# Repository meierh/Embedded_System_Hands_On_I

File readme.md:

# ESHO1 Group 07

## Group Project

All files related to the group project can be found in the `Project` folder. It contains the following parts of our project:

- [PCB Design](./Project/PCB)
- [Case Design](./Project/Case)
- Software
  - [High-Level Software with emulated hardware](./Project/Software/FLTK) (developed while the PCB was not finished yet)
  - [Full Software for our custom PCB](/Project/Software/CubeMX) (extension of the high-level software to work with the custom PCB)
- [Audio Files :smile:](./Project/DFPlayerAudio/production%20files)

The project documentation can be found [here](./Project/Documentation).

## Tasks 1 - 6

The full documentation of tasks 1 - 6 can be found [here](./Documentation_Tasks_1-6.pdf). Source code and additional files for each task can be found in the respective subfolders.

## Usage

- Ensure to clone submodules too

```bash
git submodule update --init --recursive
```

## Note

`.gitignore` contains an entry to ignore the folder "LOCAL" and all of its subfolders anywhere within this project.

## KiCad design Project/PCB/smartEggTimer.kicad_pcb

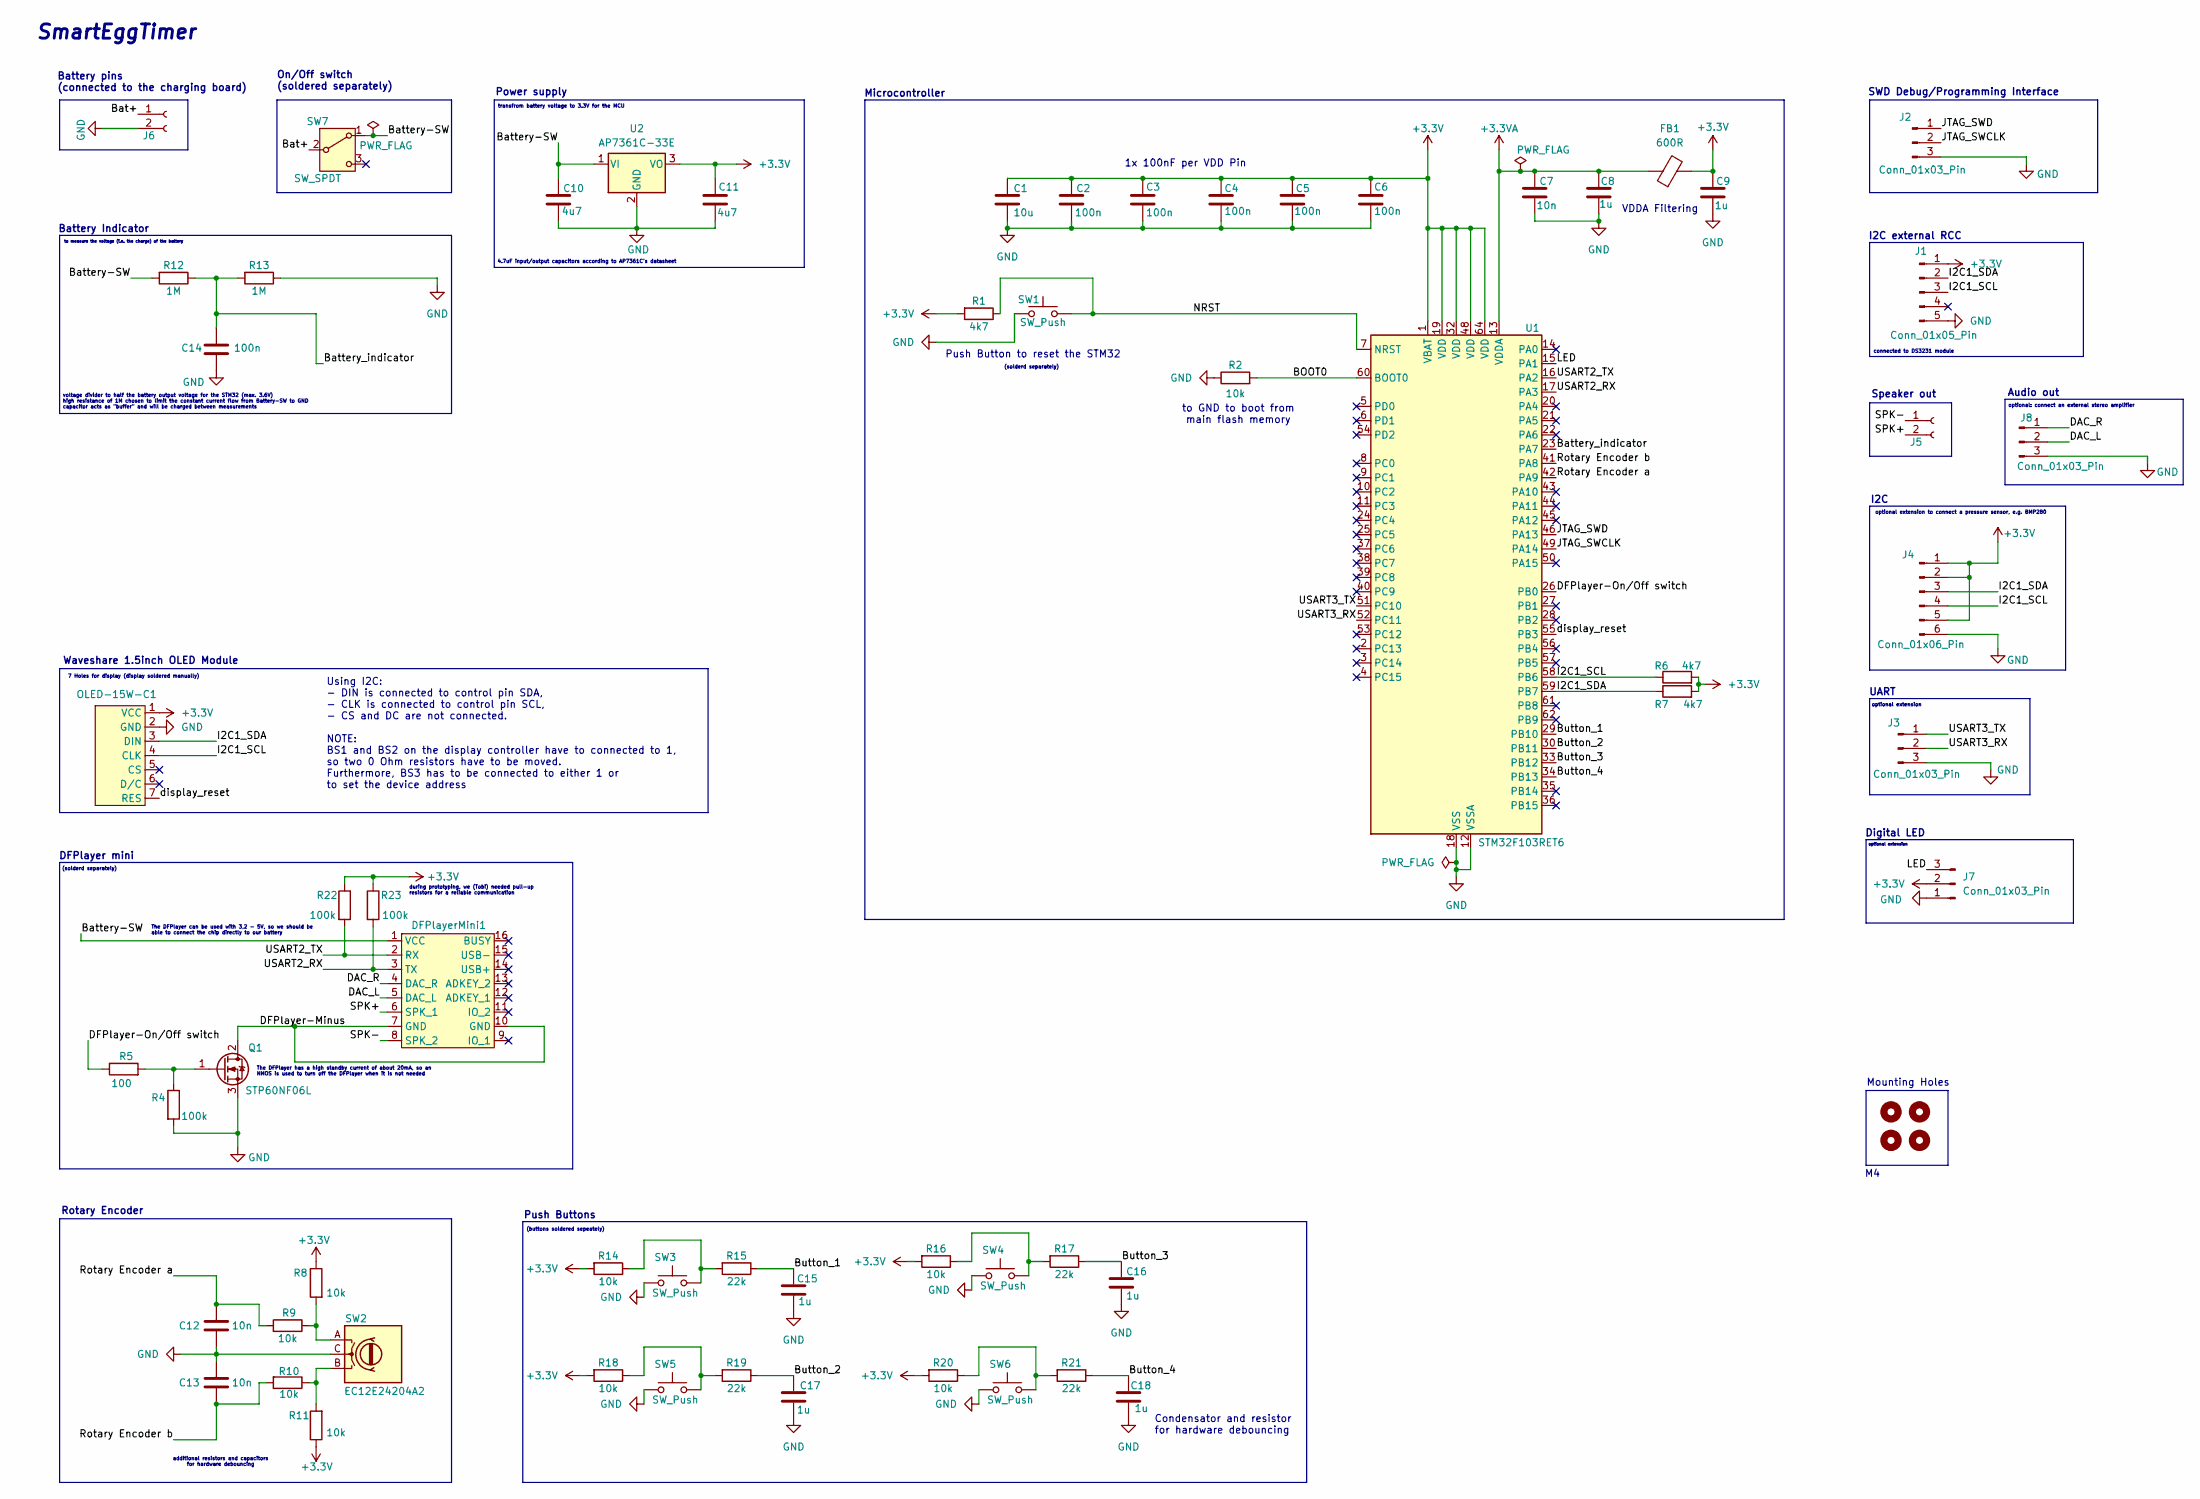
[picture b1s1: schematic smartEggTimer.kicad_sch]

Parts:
C1: 10u; C_0603_1608Metric; LCSC Part Number C19702
C2, C3, C4, C5, C6, C14: 100n; C_0402_1005Metric; LCSC Part Number C307331
C7, C12, C13: 10n; C_0402_1005Metric; LCSC Part Number C15195
C8, C9, C15, C16, C17, C18: 1u; C_0402_1005Metric; LCSC Part Number C52923
C10, C11: 4u7; C_0805_2012Metric; LCSC Part Number C1779
DFPlayerMini1: DFplayer-Mini
FB1: 600R; L_0603_1608Metric; LCSC Part Number C1002
H1, H2, H3, H8: MountingHole; MountingHole_4.3mm_M4_Without-Screws
J1: Conn_01x05_Pin; PinHeader_1x05_P2.54mm_Vertical
J2, J3, J7, J8: Conn_01x03_Pin; PinHeader_1x03_P2.54mm_Vertical
J4: Conn_01x06_Pin; PinHeader_1x06_P2.54mm_Vertical
J5, J6: Conn_01x02_Socket; PinHeader_1x02_P2.54mm_Vertical
OLED-15W-C1: PinSocket_1x07_P2.54mm_Vertical
Q1: STP60NF06L; TO-220-3_Vertical
R1, R6, R7: 4k7; R_0402_1005Metric; LCSC Part Number C25900
R2, R8, R9, R10, R11, R14, R16, R18, R20: 10k; R_0402_1005Metric; LCSC Part Number C25744
R4, R22, R23: 100k; R_0402_1005Metric; LCSC Part Number C25741
R5: 100; R_0402_1005Metric; LCSC Part Number C25076
R12, R13: 1M; R_0402_1005Metric; LCSC Part Number C26083
R15, R17, R19, R21: 22k; R_0402_1005Metric; LCSC Part Number C25768
SW1: SW_Push; SW_PUSH_6mm
SW2: EC12E24204A2; SW-TH_EC12E24204A2; LCSC Part Number C351238
SW3, SW4: SW_Push; SW_PUSH_6mm_H13mm
SW5: SW_Push; SW_PUSH_6mm_H13mm_No-Pad_Top-Right
SW6: SW_Push; SW_PUSH_6mm_H13mm_No-Pad_Top-Left
SW7: SW_SPDT; SW_Slide_SPDT_Angled_CK_OS102011MA1Q_Protruding
U1: STM32F103RET6; LQFP-64_L10.0-W10.0-P0.50-LS12.0-BL; LCSC Part Number C8322
U2: AP7361C-33E; SOT-223_L6.5-W3.5-P2.30-LS7.0-BR; LCSC Part Number C500795

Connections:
+3.3V: C1.1, C2.1, C3.1, C4.1, C5.1, C6.1, C9.1, C11.1, FB1.2, J1.1, J4.1, J4.2, J4.5, J7.2, OLED-15W-C1.1 (VCC), R1.2, R6.2, R7.2, R8.1, R11.1, R14.2, R16.2, R18.2, R20.2, R22.1, R23.1, U1.1 (VBAT), U1.19 (VDD), U1.32 (VDD), U1.48 (VDD), U1.64 (VDD), U2.3 (VO)
+3.3VA: C7.1, C8.1, FB1.1, U1.13 (VDDA)
/BOOT0: R2.2, U1.60 (BOOT0)
/Bat+: J6.1, SW7.2 (B)
/Battery-SW: C10.1, DFPlayerMini1.1 (VCC), R12.2, SW7.1 (A), U2.1 (VI)
/Battery_indicator: C14.1, R12.1, R13.2, U1.23 (PA7)
/Button_1: C15.1, R15.1, U1.29 (PB10)
/Button_2: C17.1, R19.1, U1.30 (PB11)
/Button_3: C16.1, R17.1, U1.33 (PB12)
/Button_4: C18.1, R21.1, U1.34 (PB13)
/DAC_L: DFPlayerMini1.5 (DAC_L), J8.2
/DAC_R: DFPlayerMini1.4 (DAC_R), J8.1
/DFPlayer-Minus: DFPlayerMini1.7 (GND), DFPlayerMini1.10 (GND), Q1.2 (D)
/DFPlayer-On/Off switch: R5.1, U1.26 (PB0)
/I2C1_SCL: J1.3, J4.4, OLED-15W-C1.4 (CLK), R6.1, U1.58 (PB6)
/I2C1_SDA: J1.2, J4.3, OLED-15W-C1.3 (DIN), R7.1, U1.59 (PB7)
/JTAG_SWCLK: J2.2, U1.49 (PA14)
/JTAG_SWD: J2.1, U1.46 (PA13)
/LED: J7.3, U1.15 (PA1)
/NRST: R1.1, SW1.2, U1.7 (NRST)
/Rotary Encoder a: C12.1, R9.2, U1.42 (PA9)
/Rotary Encoder b: C13.2, R10.2, U1.41 (PA8)
/SPK+: DFPlayerMini1.6 (SPK_1), J5.2
/SPK-: DFPlayerMini1.8 (SPK_2), J5.1
/USART2_RX: DFPlayerMini1.3 (TX), R23.2, U1.17 (PA3)
/USART2_TX: DFPlayerMini1.2 (RX), R22.2, U1.16 (PA2)
/USART3_RX: J3.2, U1.52 (PC11)
/USART3_TX: J3.1, U1.51 (PC10)
/display_reset: OLED-15W-C1.7 (RES), U1.55 (PB3)
GND: C1.2, C2.2, C3.2, C4.2, C5.2, C6.2, C7.2, C8.2, C9.2, C10.2, C11.2, C12.2, C13.1, C14.2, C15.2, C16.2, C17.2, C18.2, J1.5, J2.3, J3.3, J4.6, J6.2, J7.1, J8.3, OLED-15W-C1.2 (GND), Q1.3 (S), R2.1, R4.2, R13.1, SW1.1, SW2.C, SW3.1, SW4.1, SW5.1, SW6.1, U1.12 (VSSA), U1.18 (VSS), U1.31 (VSS), U1.47 (VSS), U1.63 (VSS), U2.2 (GND)
unnamed: Q1.1 (G), R4.1, R5.2
unnamed: R8.2, R9.1, SW2.A
unnamed: R10.1, R11.2, SW2.B
unnamed: R14.1, R15.2, SW3.2
unnamed: R16.1, R17.2, SW4.2
unnamed: R18.1, R19.2, SW5.2
unnamed: R20.1, R21.2, SW6.2

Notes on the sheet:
to measure the voltage (i.e. the charge) of the battery
1x 100nF per VDD Pin
Rotary Encoder
Speaker out
Waveshare 1.5inch OLED Module
Mounting Holes
optional extension
UART
transfrom battery voltage to 3.3V for the MCU
during prototyping, we (Tobi) needed pull-up resistors for a reliable communication
(solderd separately)
Microcontroller
voltage divider to half the battery output voltage for the STM32 (max. 3.6V) high resistance of 1M chosen to limit the constant current flow from Battery-SW to GND capacitor acts as "buffer" and will be charged between measurements
optional: connect an external stereo amplifier
4.7uF input/output capacitors according to AP7361C's datasheet
I2C
Power supply
(buttons soldered sepeately)
Condensator and resistor for hardware debouncing
Battery pins (connected to the charging board)
to GND to boot from main flash memory
connected to DS3231 module
Push Buttons
I2C external RCC
SmartEggTimer
DFPlayer mini
additional resistors and capacitors for hardware debouncing
SWD Debug/Programming Interface
The DFPlayer can be used with 3,2 - 5V, so we should be able to connect the chip directly to our battery
On/Off switch (soldered separately)
Push Button to reset the STM32
Audio out
VDDA Filtering
The DFPlayer has a high standby current of about 20mA, so an NMOS is used to turn off the DFPlayer when it is not needed
Battery Indicator
Using I2C: - DIN is connected to control pin SDA, - CLK is connected to control pin SCL, - CS and DC are not connected. NOTE: BS1 and BS2 on the display controller have to connected to 1, so two 0 Ohm resistors have to be moved. Furthermore, BS3 has to be connected to either 1 or to set the device 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
7 Holes for display (display soldered manually)
Digital LED
optional extension to connect a pressure sensor, e.g. BMP280

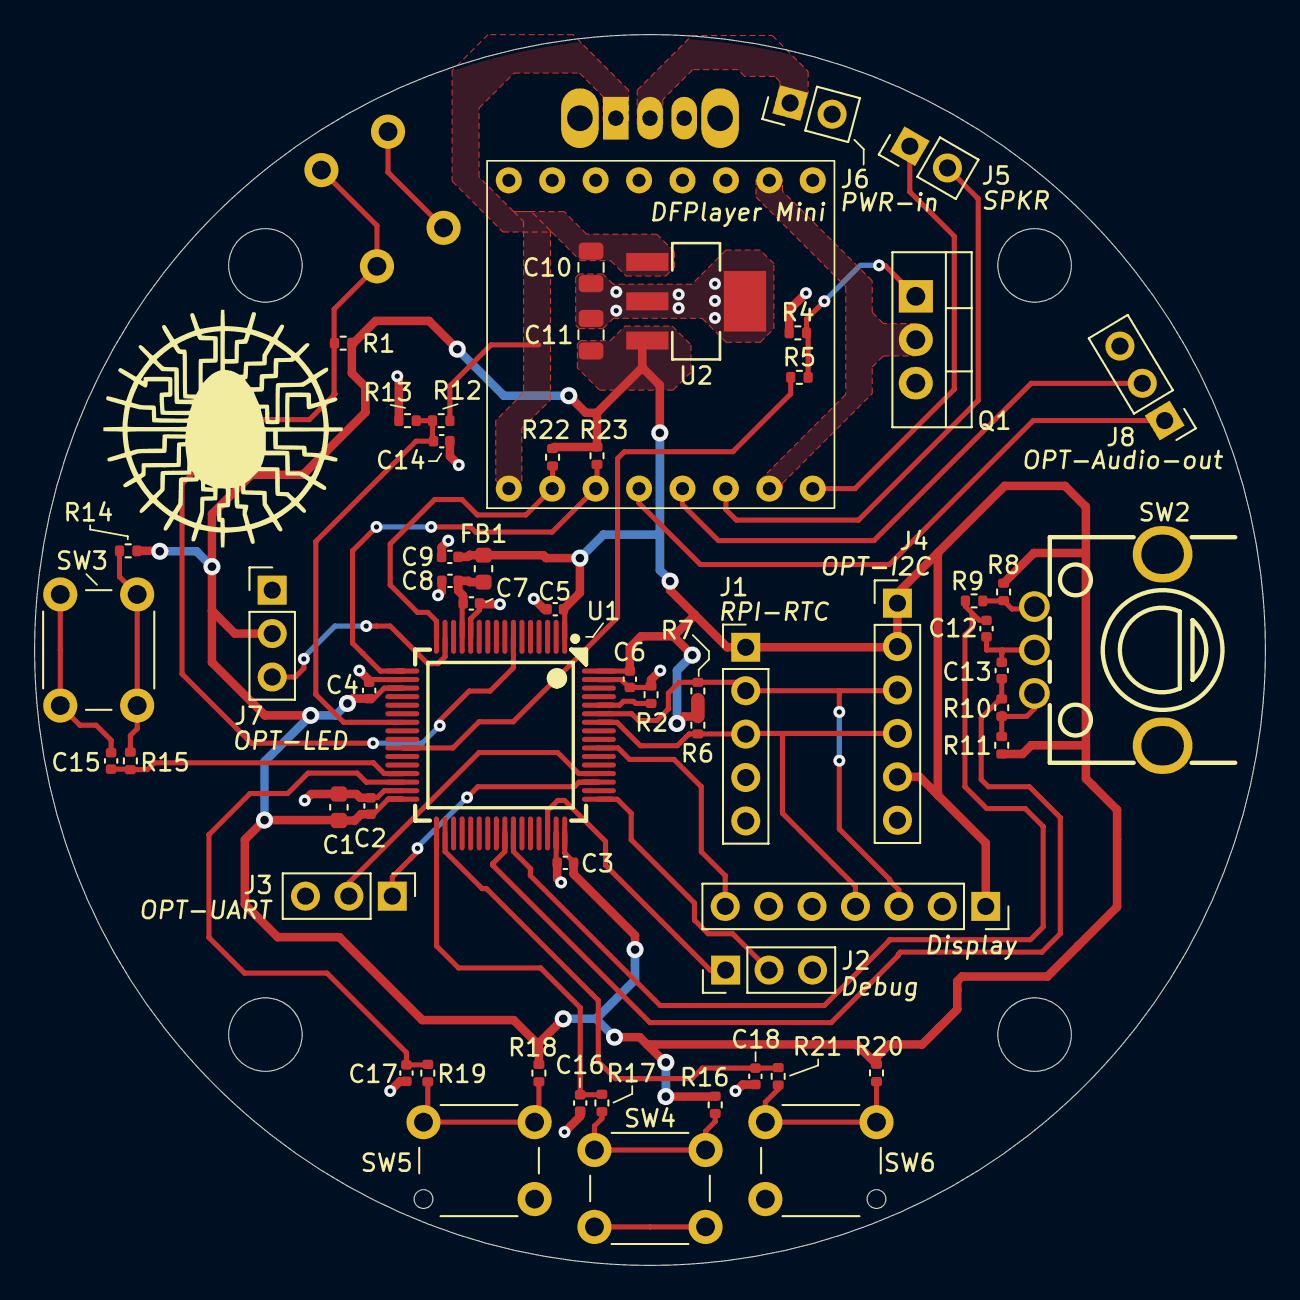
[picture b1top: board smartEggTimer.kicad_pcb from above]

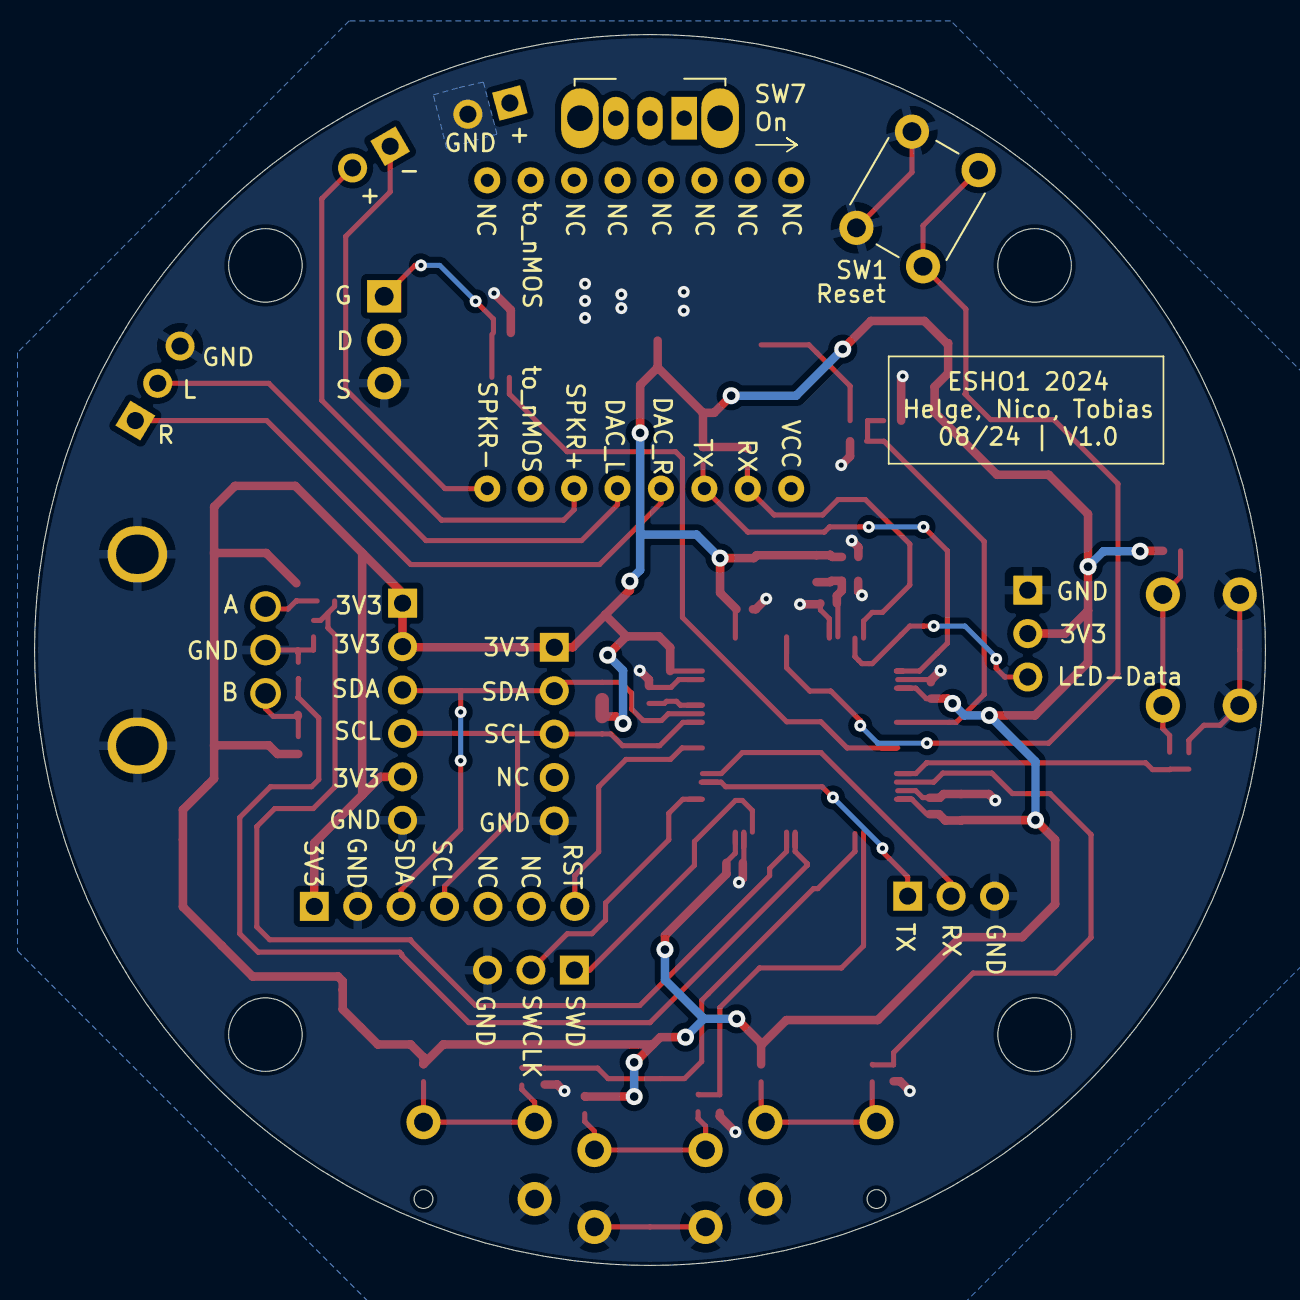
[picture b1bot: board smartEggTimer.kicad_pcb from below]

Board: 2 copper layers, 72.0 x 72.0 mm, 65 parts (2 on the bottom side), 37 nets.

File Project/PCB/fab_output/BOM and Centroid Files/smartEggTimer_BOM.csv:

"Value","Reference","Footprint","LCSC Part Number"
"10u","C1","C_0603_1608Metric","C19702"
"4u7","C10,C11","C_0805_2012Metric","C1779"
"100n","C2,C3,C4,C5,C6,C14","C_0402_1005Metric","C307331"
"10n","C7,C12,C13","C_0402_1005Metric","C15195"
"1u","C8,C9,C15,C16,C17,C18","C_0402_1005Metric","C52923"
"600R","FB1","L_0603_1608Metric","C1002"
"100","R5","R_0402_1005Metric","C25076"
"4k7","R1,R6,R7","R_0402_1005Metric","C25900"
"1M","R12,R13","R_0402_1005Metric","C26083"
"22k","R15,R17,R19,R21","R_0402_1005Metric","C25768"
"10k","R2,R8,R9,R10,R11,R14,R16,R18,R20","R_0402_1005Metric","C25744"
"100k","R4,R22,R23","R_0402_1005Metric","C25741"
"EC12E24204A2","SW2","SW-TH_EC12E24204A2","C351238"
"STM32F103RET6","U1","LQFP-64_L10.0-W10.0-P0.50-LS12.0-BL","C8322"
"AP7361C-33E","U2","SOT-223_L6.5-W3.5-P2.30-LS7.0-BR","C500795"

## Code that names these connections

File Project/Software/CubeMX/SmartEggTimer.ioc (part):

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Mcu.Name=STM32F103R(C-D-E)Tx
Mcu.Package=LQFP64
Mcu.UserName=STM32F103RETx
PA1.GPIOParameters=GPIO_Label
PA1.GPIO_Label=OPT_LED
PA1.Signal=S_TIM2_CH2
PA13.Mode=Serial_Wire
PA13.Signal=SYS_JTMS-SWDIO
PA14.Mode=Serial_Wire
PA14.Signal=SYS_JTCK-SWCLK
PA2.GPIOParameters=GPIO_Label
PA2.GPIO_Label=DFPlayer_USART_TX
PA2.Mode=Asynchronous
PA2.Signal=USART2_TX
PA3.GPIOParameters=GPIO_Label
PA3.GPIO_Label=DFPlayer_USART_RX
PA3.Mode=Asynchronous
PA3.Signal=USART2_RX
PA7.GPIOParameters=GPIO_Label
PA7.GPIO_Label=Battery_Indicator
PA7.Signal=ADCx_IN7
PA8.GPIOParameters=GPIO_Label,GPIO_ModeDefaultEXTI
PA8.GPIO_Label=Rotary_Encoder_B
PA8.GPIO_ModeDefaultEXTI=GPIO_MODE_IT_RISING_FALLING
PA8.Signal=GPXTI8
PA9.GPIOParameters=GPIO_Label,GPIO_ModeDefaultEXTI
PA9.GPIO_Label=Rotary_Encoder_A
PA9.GPIO_ModeDefaultEXTI=GPIO_MODE_IT_RISING_FALLING
PA9.Signal=GPXTI9
PB0.GPIOParameters=GPIO_Label
PB0.GPIO_Label=DFPlayer_On_Off
PB0.Signal=GPIO_Output
PB10.GPIOParameters=GPIO_Label,GPIO_ModeDefaultEXTI
PB10.GPIO_Label=Button_1
PB10.GPIO_ModeDefaultEXTI=GPIO_MODE_IT_FALLING
PB10.Signal=GPXTI10
PB11.GPIOParameters=GPIO_Label,GPIO_ModeDefaultEXTI
PB11.GPIO_Label=Button_2
PB11.GPIO_ModeDefaultEXTI=GPIO_MODE_IT_FALLING
PB11.Signal=GPXTI11
PB12.GPIOParameters=GPIO_Label,GPIO_ModeDefaultEXTI
PB12.GPIO_Label=Button_3
PB12.GPIO_ModeDefaultEXTI=GPIO_MODE_IT_FALLING
PB12.Signal=GPXTI12
PB13.GPIOParameters=GPIO_Label,GPIO_ModeDefaultEXTI
PB13.GPIO_Label=Button_4
PB13.GPIO_ModeDefaultEXTI=GPIO_MODE_IT_FALLING
PB13.Signal=GPXTI13
PB3.GPIOParameters=GPIO_Label
PB3.GPIO_Label=Display_Reset
PB3.Signal=GPIO_Output
PB6.Mode=I2C
PB6.Signal=I2C1_SCL
PB7.Mode=I2C
PB7.Signal=I2C1_SDA
PC10.GPIOParameters=GPIO_Label
PC10.GPIO_Label=OPT_UART_TX
PC10.Mode=Asynchronous
PC10.Signal=USART3_TX
PC11.GPIOParameters=GPIO_Label
PC11.GPIO_Label=OPT_UART_RX
PC11.Mode=Asynchronous
PC11.Signal=USART3_RX
RCC.SYSCLKFreq_VALUE=64000000
RCC.SYSCLKSource=RCC_SYSCLKSOURCE_PLLCLK
board=custom

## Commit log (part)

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2024-05-05 init readme
2024-05-06 create docu file for task 1
2024-05-06 Initial documentation of tasks 1.1-1.3; Content can be transfered to readme.md
2024-05-07 replace placeholder with correct pins
2024-05-08 transfer docu from file Documentation_Task1 and add add docu for openocd
2024-05-08 fix wrong pins
2024-05-08 Added start of Task2
2024-05-10 fix formatting and add git checkout for openocd
2024-05-10 Started Task 2
2024-05-10 Corrected Makefile
2024-05-10 add git checkout for openocd, fix typo and add source for the swd pins
2024-05-12 fix wrong oder of commands
2024-05-14 add gitignore
2024-05-14 Revert "test commit"
    This reverts commit c60a78df91cb033de778c94403dcbb33934f72db.
2024-05-16 extend involved pins documentation, add minor cosmetical fixes
2024-05-16 update gitignore to exclude "LOCAL" folders everywhere
2024-05-16 update and complete kernel compilation on a x86 machine
2024-05-16 extend documentation for compiling kernel locally on raspberry pi
2024-05-17 fix typo
2024-05-17 first try for openocd command
2024-05-17 exculde build folder
2024-05-17 complete Makefile
2024-05-17 first try to turn on LED
2024-05-17 Removed binary
2024-05-17 Corrected LED set
2024-05-18 fix led code
2024-05-23 add info about important and used register
2024-05-23 WIP code for blinking with joystick
2024-05-23 fix wrong joystick pins
2024-05-24 Implemented SWD; expanded 3.2 and 3.3
2024-05-24 Added wiringPi library to 3.1
2024-05-24 Completed SWD implementation; Not yet tested
2024-05-25 add target "halt" to stop the M0
2024-05-25 fix comment
2024-05-25 change target to "reset" which now also deletes the program currently stored on the M0
2024-05-27 Revert "change target to "reset" which now also deletes the program currently stored on the M0"
    This reverts commit d53b472ddca374d858eb29c3391ab75fe14e6dbb.
    Deleting the currently stored program did not work correctly but instead lead to a problem where the program was not executed properly anymore after a reboot of the Raspberry Pi. Thus, remove non-wor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
2024-06-06 Worked on 5.1 and 5.3
2024-06-06 Skeleton of 4.2
2024-06-06 blinky: fix blinking rate, restructure, add comments
2024-06-06 add explanation about device-independant CMSIS header file
2024-06-06 ignore vscode settings
2024-06-06 add comment about compilation of task 1 instead of task 2
2024-06-06 update main to turn on all leds
2024-06-06 add comment
2024-06-07 add environment for task 4_1
2024-06-08 fix off by one error on prescaler
2024-06-08 finish implementing better-blinky
2024-06-14 Work on 5.1
2024-06-17 Ableiten von Bildern und daten für 5.1 und 5.3
2024-06-17 Digital Filter implementation 5.4
2024-06-20 implement better blinky with HAL
2024-06-24 start fixing SWD implementation - initialisation works now
    More fixes needed
2024-06-26 add code for UART communication
2024-06-26 fix typos
2024-06-26 more fixes on SWD implementation Repetitive IDCODE reads work now
2024-06-26 add openocd config file for clarity
2024-06-26 changed my mind (:
2024-06-26 some minor cosmetical fixes
2024-06-28 More work done
2024-07-04 exclude KiCad backups and lock files
2024-07-04 ignore more KiCad files
2024-07-06 Done 5.2 apart from last section
2024-07-06 Added model to LED, Transistor and VSOURCE
2024-07-11 finish 3.3
2024-07-11 add stdout of IDCODE and delete untested read/write calls
2024-07-11 add some info about the execution of our SWD implementation
2024-07-11 Expanded 6
2024-07-12 expand explanation
2024-07-12 Changed FIR Filter to microcontroller settings
2024-07-13 troubleshoot debugging with CLion
2024-07-14 add wip task 4.3
2024-07-16 add config register addresses and add remaining methods for reading the sensor
2024-07-16 fix sensor operations add methode to enable the sensor
2024-07-16 fix i2c communication
2024-07-16 add barometer test calls
2024-07-16 add wip files for magnetometer and gyro & accelerometer
2024-07-17 implement magnetometer
2024-07-17 extend sensortest
2024-07-17 add placeholder to read converted sensor values
2024-07-17 add register addresses and add list of references
2024-07-18 Work on 6)
2024-07-22 Fixed 6 KiCAD
2024-07-22 implement dimming onboard LED via PWM
2024-07-22 implement PWM signal on U6 BJT (M4)
2024-07-22 Completed 6) Simulation and Measurement
2024-07-23 add new barometer implementation
2024-07-23 add new implementation for v3 Accelerometer/Magnetometer
2024-07-23 adapt LSM6DS33 implementation to new project structure
2024-07-23 fix stupid error
2024-07-23 adapt LIS3MDL implementation to new project structure
2024-07-23 move old implementations out of the source folder
2024-07-23 implement auto-detection of the sensor board
2024-07-23 add simple test code
2024-07-24 add documentation about v3 sensor board
2024-07-24 refine UART implementation and switch project structure to CMake
2024-07-26 add pin description
2024-07-26 fix off-by-one error with timer's ARR
2024-07-26 add new pwm implementation for task 6
2024-07-26 add wip implementation of task 4.4
2024-07-26 refactor folder structure and delete unused code
2024-07-26 move images to folder
2024-07-26 remove pull-up resistor settings for joystick Pull-up resistors are already implemented on the ESA extension board.
2024-07-26 add some comments
2024-07-26 change HAL_Blinky's project structure to CMake and add some minor corrections Corrections encompass - Off-by-one error at Auto-Reload Register - Enabling Timer's URS s.t. it only causes interrupts at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
2024-07-26 update toolchain to STM32CubeIDE s.t. CLion stops complaining :)
2024-07-26 remove some leftover generated files
2024-07-26 add joystick pins
2024-07-26 add UART interrupts
2024-07-26 update system clock config
2024-07-26 reformat
2024-07-27 enable continuous mode and change sample rate for better results
2024-07-27 implement calibration in a separate class as required in the task
2024-07-27 complete implementation of light_sensor and light_sensor_calibration
2024-07-27 add bounds check, status leds and measure multiple values upon calibration
2024-07-27 add UART functionality
2024-07-27 add documentation on 4.1 and 4.4
2024-07-28 Filter postprocessing
2024-07-29 change folder structure
2024-07-29 add references to folders
2024-07-29 start formatting
2024-07-30 resolve merge conflict
2024-07-30 minor cleanup
2024-07-30 use new filter and some minor cleanup
2024-07-30 implement improved brightness steps
2024-07-30 add docu for improved brightness steps
2024-07-30 fix off by one error
2024-07-30 Added measurement protocol
2024-07-31 add more simulation plots and extend documentation of 5.1
2024-07-31 add formatting / fix some typos
2024-07-31 add cut-off frequencies to smoothed diagrams
2024-07-31 add some formatting
2024-07-31 remove redundant headline
2024-07-31 add simulation and measurement of current through LED
2024-07-31 remove outdated I2C code
2024-07-31 update formatting for MarkText
2024-07-31 add pdf version of readmes
2024-07-31 add full documentation as pdf
2024-08-06 Software and Hardware Emulator
2024-08-08 add wip pcb
2024-08-12 Adds to software
2024-08-14 add footprints for DFPlayer and fix error
2024-08-14 fix buttons, finish rotary encoder, add battery indicator
2024-08-16 fix annotation, add resistor to mosfet, remove debug power supply, use new voltage regulator and choose footprints
2024-08-16 cosmetic improvements
2024-08-18 basic planing
2024-08-18 minor fixes
2024-08-19 Initial SmartEgg§
2024-08-19 Implemeted alarm
2024-08-19 corrections and refinements for the schematic
2024-08-19 add DAC out
2024-08-19 add cubeMX project
2024-08-19 add pin numbers for display
2024-08-19 add 3D model for rotary encoder
2024-08-19 add another UART interface
2024-08-19 rough positioning
2024-08-20 More applications
2024-08-21 Started Snake
2024-08-21 add GND pins for SWD and optional UART
2024-08-23 add exact positioning of critical parts (switches, rotary encoder and drill holes need to fit to the 3D design of the case)
2024-08-23 rework DFPlayer section based on prototyping - add pull-up resistors for UART communication - add a pin header for the input voltage
2024-08-25 placement of all components & initial routing
2024-08-26 finish PCB routing Further changes: - Change schematic symbol of MOSFET s.t. pin assignment is correct - Add STEP file for DFPlayer Mini - Save edited footprints to custom-parts project library - Set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
2024-08-26 re-export step file
2024-08-26 minor fixes on DFPlayer pin labels
2024-08-27 Modified Space Invaders
2024-08-27 generate files for manufacturing
2024-08-27 add manufacturing files explanation
2024-08-28 modify export paths
2024-08-29 replace footprints with JLCs' footprints
2024-08-29 add JLCPCB specifications/options
2024-08-29 add logo
2024-09-16 fix compilation on MacOS
2024-09-16 update CubeMX configuration and refine repository structure
2024-09-16 add basic project structure generated by CubeMX
2024-09-16 add OpenOCD configuration and basic readme
2024-09-16 add Peripheral folder
2024-09-16 add Peripheral folder properly
2024-09-16 remove example code from main
2024-09-16 add driver for RTC, add driver for Display, add System for STM32, handle interrupts
2024-09-16 add Datetime class
2024-09-16 set I2C to fast mode
2024-09-17 use new Datetime class, fix missing pin defs, delete duplicate System class, fix typo
2024-09-18 Added clock setting app; Augmented applications for changes system methods
2024-09-19 add tim3, change hardware to pointer to avoid hard fault, increase stm clock to 64 Mhz
2024-09-19 add delay after init (maybe not necessary), rotate image in correct position, use new Font enum
2024-09-19 fix tim3
2024-09-19 Added testimage app / removed display method from constructor
2024-09-19 Added iostream header
2024-09-19 Move header
2024-09-20 remove delay
2024-09-20 comment out setup stuff because of problems
2024-09-20 fix typo, add cstdint
2024-09-20 implement faster screen updater
2024-09-20 update apps
2024-09-20 fix signal of rotary encoder (wip), add work call in interrupt, fix wrong implemented DisplayItem::Empty, stop interrupts before changing the mode, fix out of bounds handling in the display lib
2024-09-20 rollback cmake version
2024-09-22 add method definitions to control the DFPlayer
2024-09-22 Bug fixes and alarms implemented
2024-09-22 increase priority of SysTick interrupts
2024-09-22 Added MP3 app; Added visual alarms; Added alarm sound activations; Removed bugs
2024-09-22 Fixed time representation bug
2024-09-22 import Helge's changes
2024-09-22 remove games
2024-09-22 move PCB files one folder up
2024-09-22 add implementation for DFPlayer and restructure Peripheral folder
2024-09-22 increase SWD speed
2024-09-23 add audio files for DFPlayer
2024-09-23 implement interface to DFPlayer
2024-09-23 add adjustable timeout for UART transmit/receive to avoid unwanted blocking
2024-09-23 initialize volume
2024-09-23 Changed MP3 Player volume display
2024-09-23 High level software UML
2024-09-23 implement rotary encoder
2024-09-23 increase EXTI[9:5] preemption priority
2024-09-23 fix EXTI mode for encoder pins
2024-09-23 fix uint underflow
2024-09-23 init DFPlayer for MP3 mode
2024-09-23 init DFPlayer properly this time
2024-09-24 decrease sampling rate for DFPlayer audio files and increase update interval
2024-09-24 add readme for DFPlayer audio files
2024-09-24 add parameter to turn on/off initialization of DFPlayer
2024-09-24 small UI improvements
2024-09-24 fix set-time methode
2024-09-24 Fixed MP3 play status bug
2024-09-24 change rotary encoder debouncing
2024-09-24 fix some minor MP3 player bugs
2024-09-24 premature fix for battery bars
2024-09-24 fix ADC initilization
2024-09-25 Change battery display design
2024-09-25 fix datetime
2024-09-25 add images for documentation
2024-09-25 implement BSOD
2024-09-25 implement usages of BSOD
2024-09-25 add Handout folder
2024-09-25 Upload New File
2024-09-25 remove TestImage app from app selection
2024-09-25 restructure schematic
2024-09-25 move images to subfolders
2024-09-25 add PCB exports
2024-09-25 add handouts
2024-09-25 add information about measurement of the battery voltage curve
2024-09-25 rename to readme.md
2024-09-25 rotate logo
2024-09-26 fix UI
2024-09-26 add CAD
2024-09-26 adapt writeIniTemp() to boundaries
2024-09-26 add stronger debouncing for rotary encoder
2024-09-26 add support to change volume while MP3 player is uninitialized
2024-09-27 move images of software to a subfolder
2024-09-27 add project documentation as pdf
2024-09-27 reduce file size
2024-09-27 add references to project documentation and project files to top-level readme
